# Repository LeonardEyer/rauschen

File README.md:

# Rauschen

Realtime adaptive filtering for modular synthesis using a teensy.
More about the general principle of adaptive filtering as synthesis technique: [Here](Idea.pdf)

## Getting Started

Fetch this repository using ```git clone ```

### Prerequisites

* Teensy 4.0

* Matching teensy audio shield

* Connect teensy via USB

* [Install](https://platformio.org/platformio-ide) PIO

* Edit PIO [config](platformio.ini) and set desired deployment target (Teensy 4.0 default)

### Building the Filter

Check the [schematics](hardware/Filter_V0.2.sch)

<!-- ### Installing

A step by step series of examples that tell you how to get a development env running

Say what the step will be

```
Give the example
```

And repeat

```
until finished
```

End with an example of getting some data out of the system or using it for a little demo -->

<!-- ## Running the tests

Explain how to run the automated tests for this system -->

<!-- ### Break down into end to end tests

Explain what these tests test and why

```
Give an example
```

### And coding style tests

Explain what these tests test and why

```
Give an example
``` -->

## How does it work
* [Documentation](https://leonardeyer.github.io/rauschen/)

## Deployment

Deploy using PIO

## Authors

* **Victor Höller** - *Schematics and PCB design*
* **Leonard Eyer** - *Programming*

## License

This project is licensed under the Apache License - see the [LICENSE.md](LICENSE.md) file for details

<!-- ## Acknowledgments

* Hat tip to anyone whose code was used
* Inspiration
* etc -->

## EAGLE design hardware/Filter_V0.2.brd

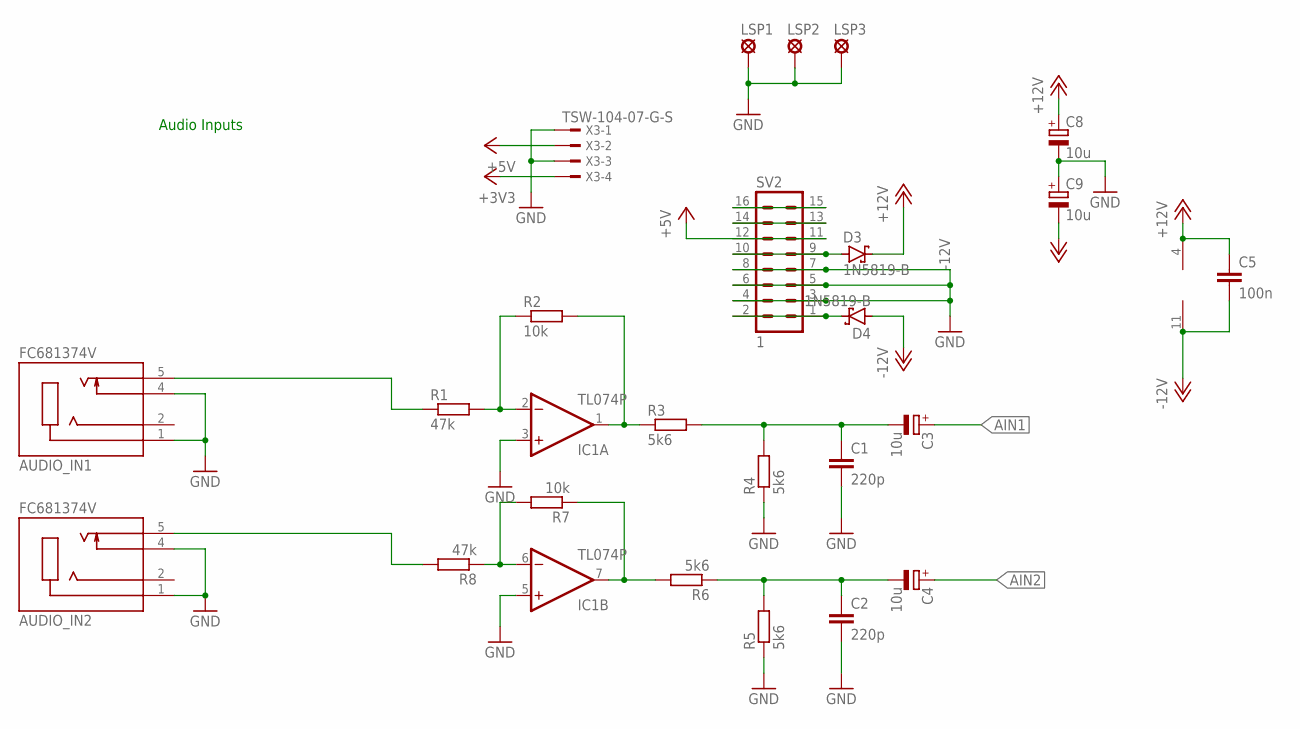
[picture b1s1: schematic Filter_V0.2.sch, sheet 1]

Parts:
AUDIO_IN1, AUDIO_IN2: FC681374V; CLIFF_FC681374V
C1, C2: 220p; C025-024X044
C3, C4, C8, C9: 10u; E2,5-7
C5: 100n; C025-024X044
D3, D4: 1N5819-B; DO41-7.6
IC1: TL074P; DIL14
LSP1, LSP2, LSP3: LSP10
R1, R8: 47k; 0204/7
R2, R7: 10k; 0204/7
R3, R4, R5, R6: 5k6; 0204/7
SV2: 1; ML16
X3: TSW-104-07-G-S; TSW-104-XX-G-S

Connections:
+3V3: X3.4; also elsewhere on the board
+5V: SV2.11, SV2.12, X3.2; also elsewhere on the board
+12V: C5.1, C8.+, D3.C, IC1.4 (V+)
-12V: C5.2, C9.-, D4.A, IC1.11 (V-)
AIN1: C3.+; also elsewhere on the board
AIN2: C4.+; also elsewhere on the board
GND: AUDIO_IN1.1, AUDIO_IN1.4, AUDIO_IN2.1, AUDIO_IN2.4, C1.2, C2.2, C8.-, C9.+, IC1.3 (+IN), IC1.5 (+IN), LSP1.MP, LSP2.MP, LSP3.MP, R4.1, R5.1, SV2.3, SV2.4, SV2.5, SV2.6, SV2.7, SV2.8, X3.1, X3.3; also elsewhere on the board
unnamed: IC1.6 (-IN), R7.2, R8.1
unnamed: IC1.1 (OUT), R2.2, R3.1
unnamed: C1.1, C3.-, R3.2, R4.2
unnamed: IC1.7 (OUT), R6.2, R7.1
unnamed: C2.1, C4.-, R5.2, R6.1
unnamed: IC1.2 (-IN), R1.2, R2.1
unnamed: AUDIO_IN1.5, R1.1
unnamed: AUDIO_IN2.5, R8.2
unnamed: D3.A, SV2.9, SV2.10
unnamed: D4.C, SV2.1, SV2.2
unnamed: SV2.13, SV2.14
unnamed: SV2.15, SV2.16

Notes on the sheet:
Audio Inputs

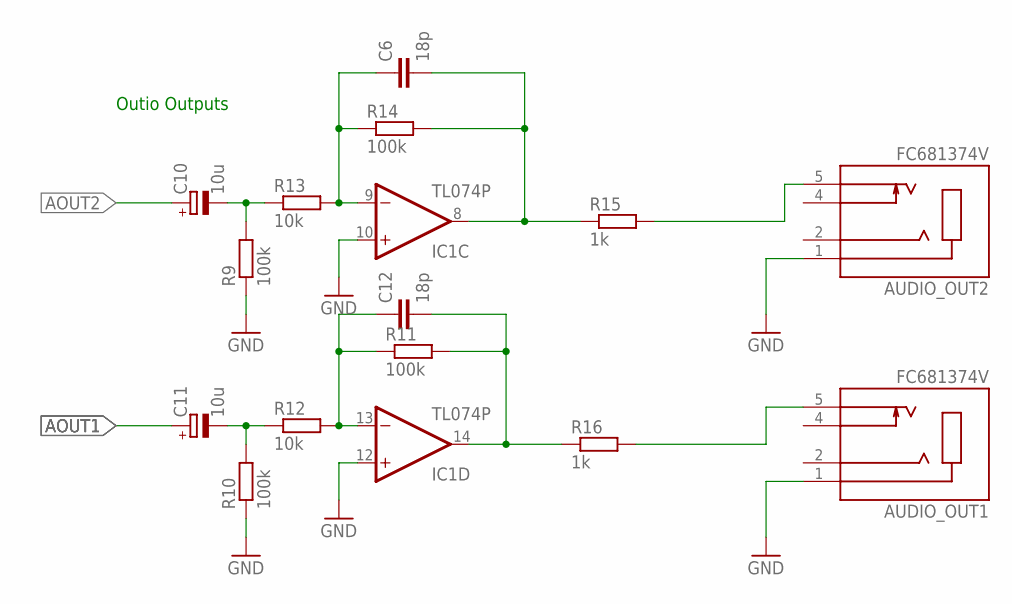
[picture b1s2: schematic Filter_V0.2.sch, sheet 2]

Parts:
AUDIO_OUT1, AUDIO_OUT2: FC681374V; CLIFF_FC681374V
C6, C12: 18p; C025-024X044
C10, C11: 10u; E2,5-7
IC1: TL074P; DIL14
R9, R10, R11, R14: 100k; 0204/7
R12, R13: 10k; 0204/7
R15, R16: 1k; 0204/7

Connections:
AOUT1: C11.+; also elsewhere on the board
AOUT2: C10.+; also elsewhere on the board
GND: AUDIO_OUT1.1, AUDIO_OUT2.1, IC1.10 (+IN), IC1.12 (+IN), R9.1, R10.1; also elsewhere on the board
unnamed: C6.1, IC1.9 (-IN), R13.2, R14.1
unnamed: C6.2, IC1.8 (OUT), R14.2, R15.1
unnamed: C12.1, IC1.13 (-IN), R11.1, R12.2
unnamed: C12.2, IC1.14 (OUT), R11.2, R16.1
unnamed: AUDIO_OUT1.5, R16.2
unnamed: AUDIO_OUT2.5, R15.2
unnamed: C10.-, R9.2, R13.1
unnamed: C11.-, R10.2, R12.1

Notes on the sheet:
Outio Outputs

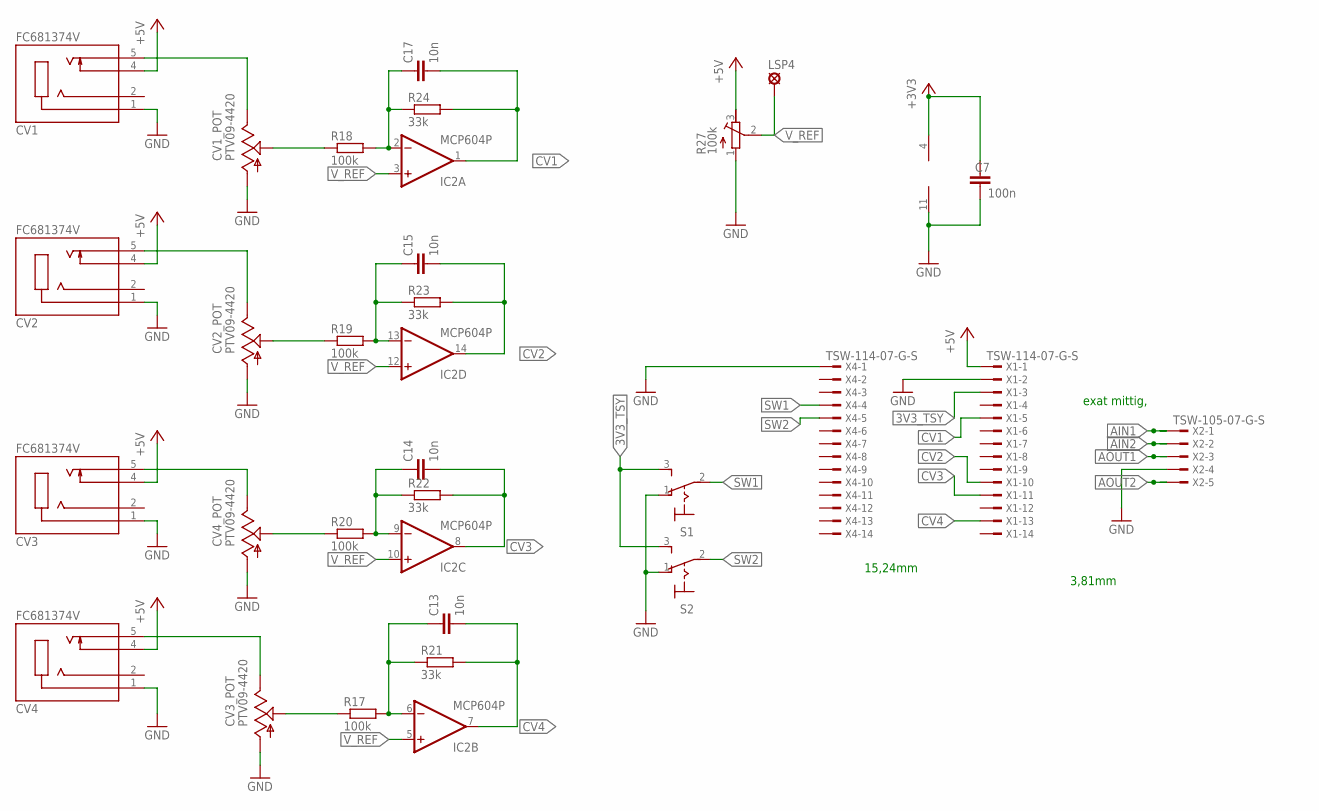
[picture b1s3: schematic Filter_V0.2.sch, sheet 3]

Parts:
C7: 100n; C025-024X044
C13, C14, C15, C17: 10n; C025-024X044
CV1, CV2, CV3, CV4: FC681374V; CLIFF_FC681374V
CV1_POT, CV2_POT, CV3_POT, CV4_POT: PTV09-4420; PTV09
IC2: MCP604P; DIL14
LSP4: LSP10
R17, R18, R19, R20: 100k; 0204/7
R21, R22, R23, R24: 33k; 0204/7
R27: 100k; RTRIM64W
S1, S2: M9040P
X1, X4: TSW-114-07-G-S; TSW-114-XX-G-S
X2: TSW-105-07-G-S; TSW-105-XX-G-S

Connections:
3V3_TSY: S1.3 (S), S2.3 (S), X1.3
+3V3: C7.1, IC2.4 (V+); also elsewhere on the board
+5V: CV1.4, CV2.4, CV3.4, CV4.4, R27.3 (E), X1.1; also elsewhere on the board
AIN1: X2.1; also elsewhere on the board
AIN2: X2.2; also elsewhere on the board
AOUT1: X2.3; also elsewhere on the board
AOUT2: X2.5; also elsewhere on the board
CV1: C17.2, IC2.1 (OUT), R24.2, X1.5
CV2: C15.2, IC2.14 (OUT), R23.2, X1.10
CV3: C14.2, IC2.8 (OUT), R22.2, X1.11
CV4: C13.2, IC2.7 (OUT), R21.2, X1.13
GND: C7.2, CV1.1, CV1_POT.1 (A), CV2.1, CV2_POT.1 (A), CV3.1, CV3_POT.1 (A), CV4.1, CV4_POT.1 (A), IC2.11 (V-), R27.1 (A), S1.1 (O), S2.1 (O), X1.2, X2.4, X4.1; also elsewhere on the board
unnamed: C13.1, IC2.6 (-IN), R17.2, R21.1
unnamed: C14.1, IC2.9 (-IN), R20.2, R22.1
unnamed: C15.1, IC2.13 (-IN), R19.2, R23.1
unnamed: C17.1, IC2.2 (-IN), R18.2, R24.1
unnamed: CV4_POT.2 (S), R20.1
unnamed: CV2_POT.2 (S), R19.1
unnamed: CV1_POT.2 (S), R18.1
unnamed: CV3_POT.2 (S), R17.1
unnamed: CV1.5, CV1_POT.3 (E)
unnamed: CV2.5, CV2_POT.3 (E)
unnamed: CV3.5, CV4_POT.3 (E)
unnamed: CV3_POT.3 (E), CV4.5
SW1: S1.2, X4.4
SW2: S2.2, X4.5
V_REF: IC2.3 (+IN), IC2.5 (+IN), IC2.10 (+IN), IC2.12 (+IN), LSP4.MP, R27.2 (S)

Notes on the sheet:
15,24mm
3,81mm
exat mittig,

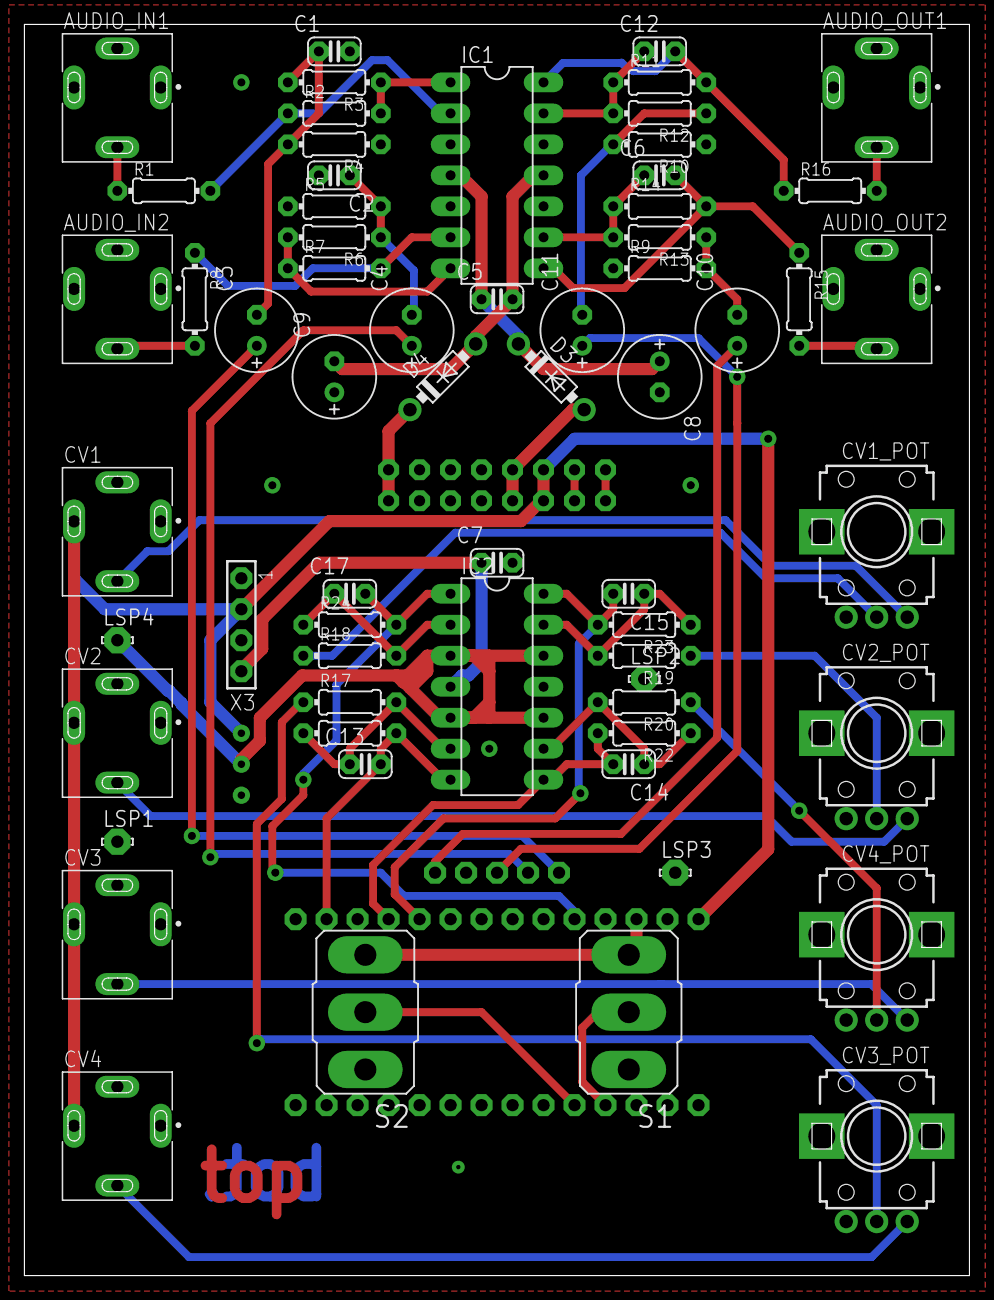
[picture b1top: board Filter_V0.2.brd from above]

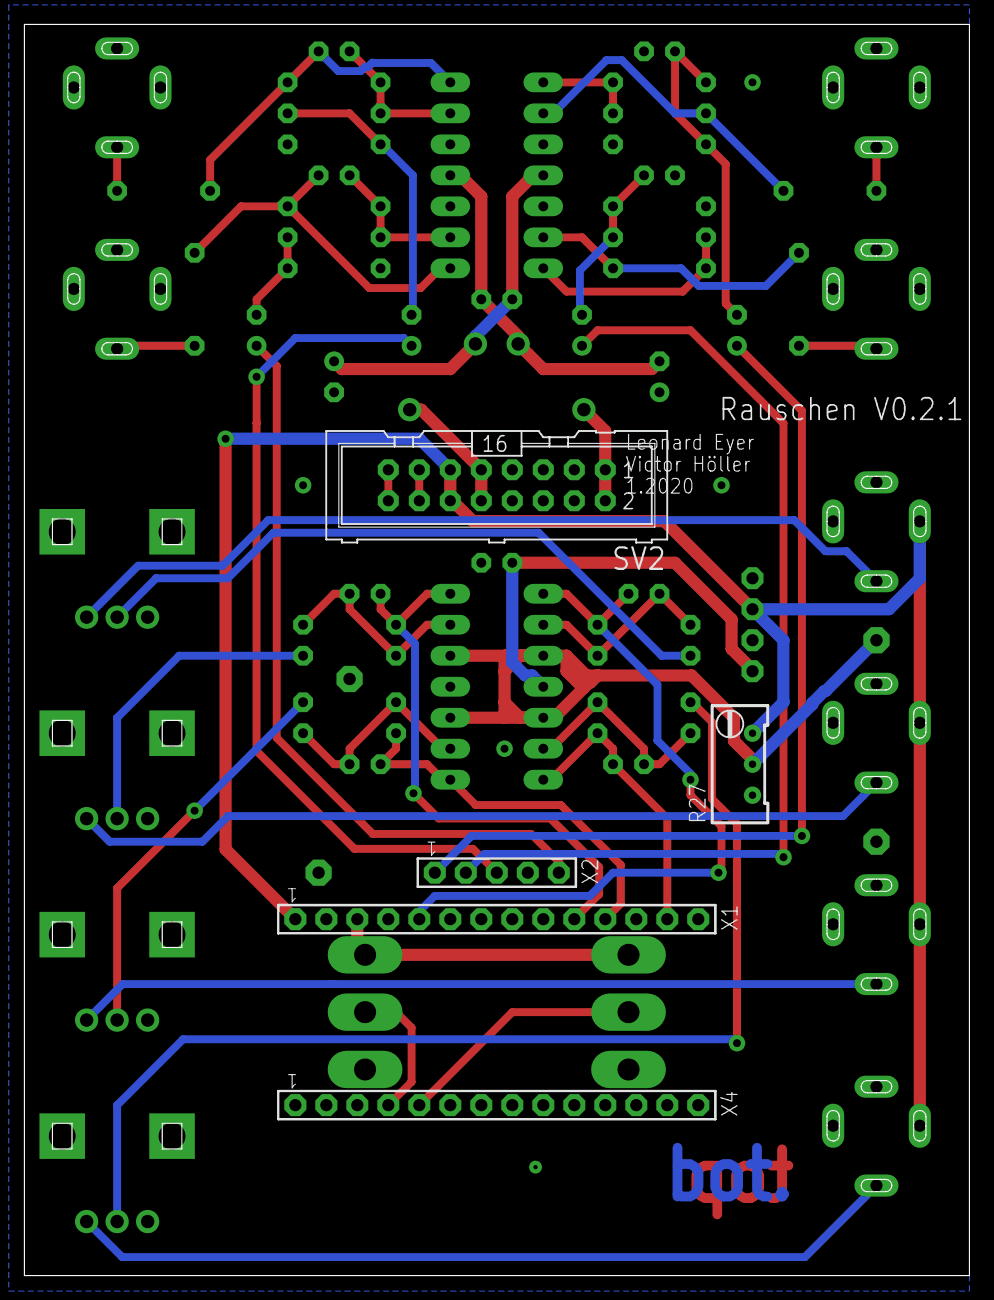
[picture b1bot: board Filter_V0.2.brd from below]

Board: 2 copper layers, 77.5 x 102.5 mm, 68 parts (5 on the bottom side), 49 nets.

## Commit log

2020-01-28 Initial state. Basic NLMS Filter with internal signal
2020-01-28 cleanup
2020-01-28 update travis
2020-01-28 remove travis
2020-01-31 Modifications to use one cv input for frequecy modulation
2020-02-05 Adaptive filtering through i2s inputs working
2020-03-12 Refactor
2020-03-12 Add readme
2020-03-12 Update readme. Add doxygen config
2020-03-12 Add documentation
2020-03-12 Ignore hidden folders
2020-03-12 Untrack vscode config
2020-03-12 Add travis yml and doxyfile
2020-03-12 Rename travis config
2020-03-12 Update doxyfile config
2020-03-12 Remove doc from master. Add doc ref to readme
2020-03-16 Add schematics
2020-03-16 Change license and teensy version
2020-03-16 Create LICENSE
2020-03-16 Add idea document
2020-03-16 Update readme to include idea
2020-03-16 Deploy LeonardEyer/rauschen to github.com/LeonardEyer/rauschen.git:gh-pages
